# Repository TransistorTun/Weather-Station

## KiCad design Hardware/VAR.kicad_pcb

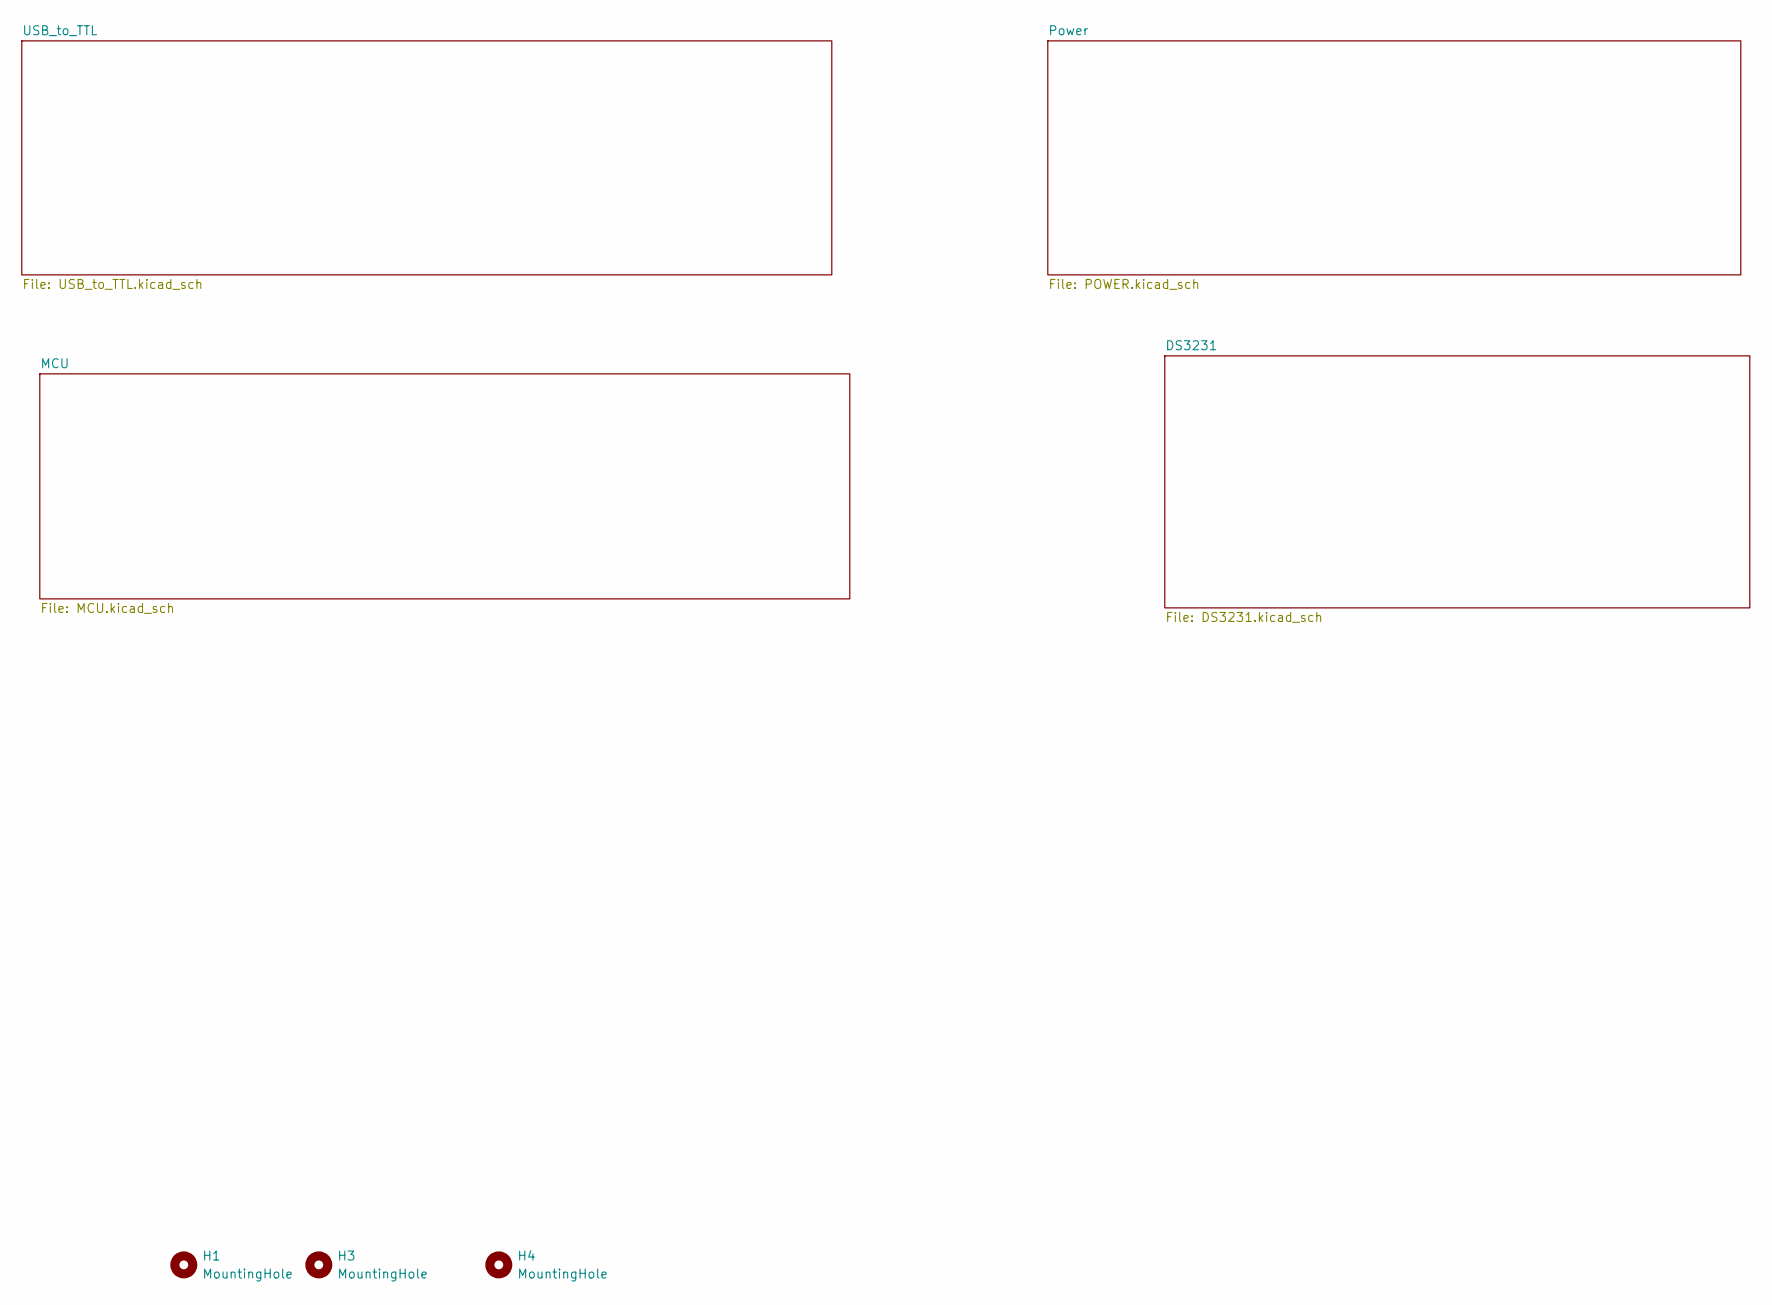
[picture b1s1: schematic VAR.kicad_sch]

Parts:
H1, H3, H4: MountingHole; MountingHole_3.2mm_M3

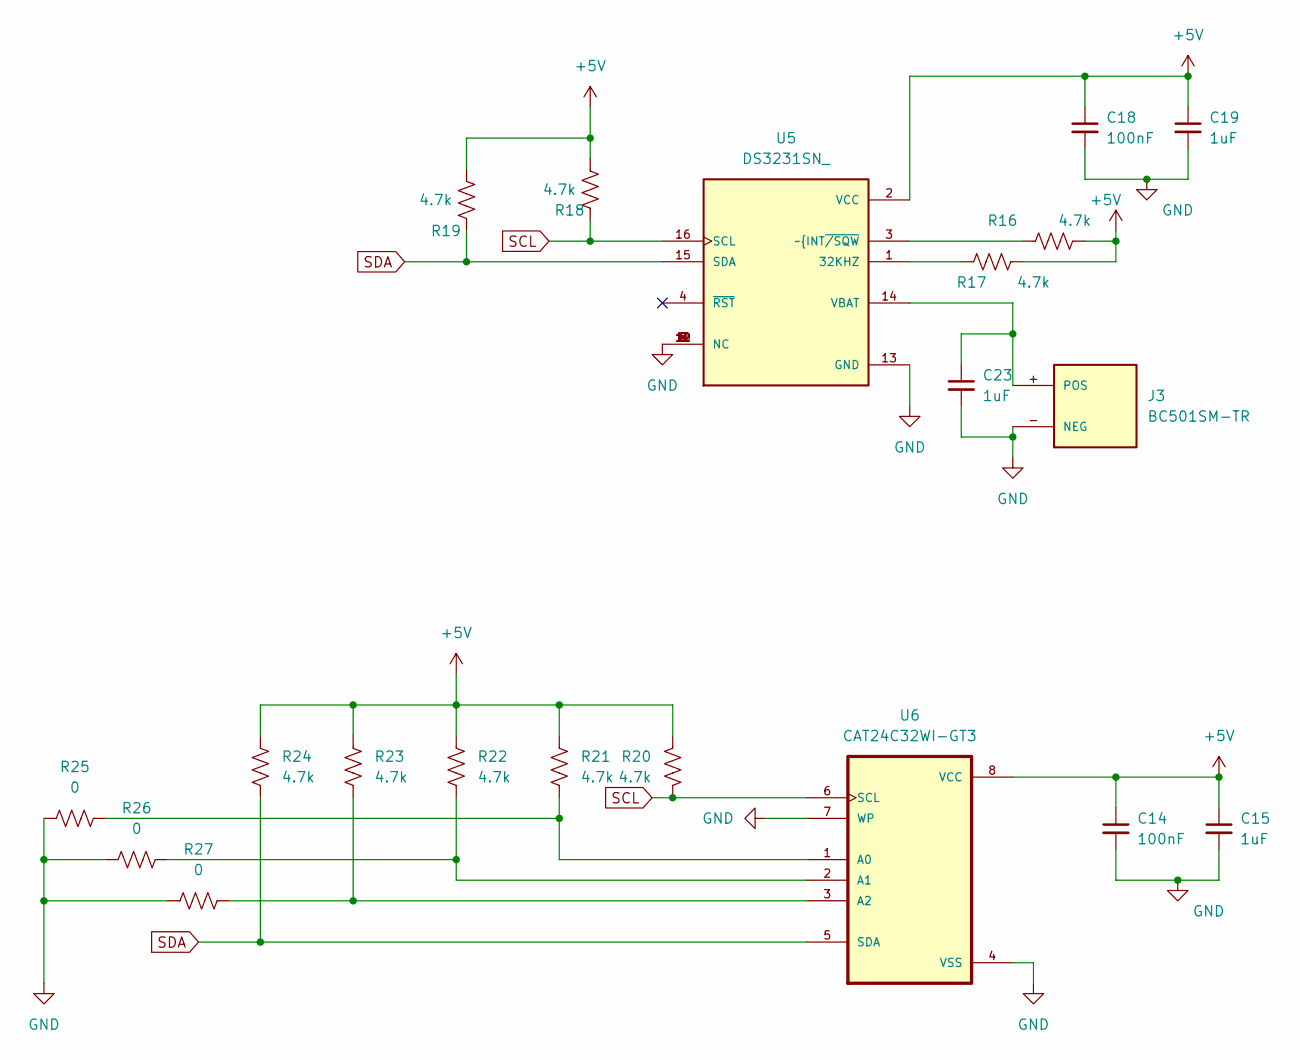
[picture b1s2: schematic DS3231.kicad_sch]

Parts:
C14, C18: 100nF; C_0805_2012Metric_Pad1.18x1.45mm_HandSolder
C15, C19, C23: 1uF; C_0805_2012Metric_Pad1.18x1.45mm_HandSolder
J3: BC501SM-TR; MPD_BC501SM-TR; PARTREV H
R16, R17, R18, R19, R20, R21, R22, R23, R24: 4.7k; R_0805_2012Metric_Pad1.20x1.40mm_HandSolder
R25, R26, R27: 0; R_0805_2012Metric_Pad1.20x1.40mm_HandSolder
U5: DS3231SN_; SOIC127P1032X265-16N; PARTREV 10
U6: CAT24C32WI-GT3; SOIC127P600X175-8N

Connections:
+5V: C14.1, C15.1, C18.1, C19.1, R16.2, R17.2, R18.2, R19.2, R20.1, R21.1, R22.1, R23.1, R24.1, U5.2 (VCC), U6.8 (VCC); also elsewhere on the board
GND: C14.2, C15.2, C18.2, C19.2, C23.2, J3.- (NEG), R25.1, R26.1, R27.1, U5.5 (NC), U5.6 (NC), U5.7 (NC), U5.8 (NC), U5.9 (NC), U5.10 (NC), U5.11 (NC), U5.12 (NC), U5.13 (GND), U6.4 (VSS), U6.7 (WP); also elsewhere on the board
unnamed: C23.1, J3.+ (POS), U5.14 (VBAT)
unnamed: R17.1, U5.1 (32KHZ)
unnamed: R16.1, U5.3 (~INT~{/SQW)
unnamed: R21.2, R25.2, U6.1 (A0)
unnamed: R22.2, R26.2, U6.2 (A1)
unnamed: R23.2, R27.2, U6.3 (A2)
SCL: R18.1, R20.2, U5.16 (SCL), U6.6 (SCL); also elsewhere on the board
SDA: R19.1, R24.2, U5.15 (SDA), U6.5 (SDA); also elsewhere on the board

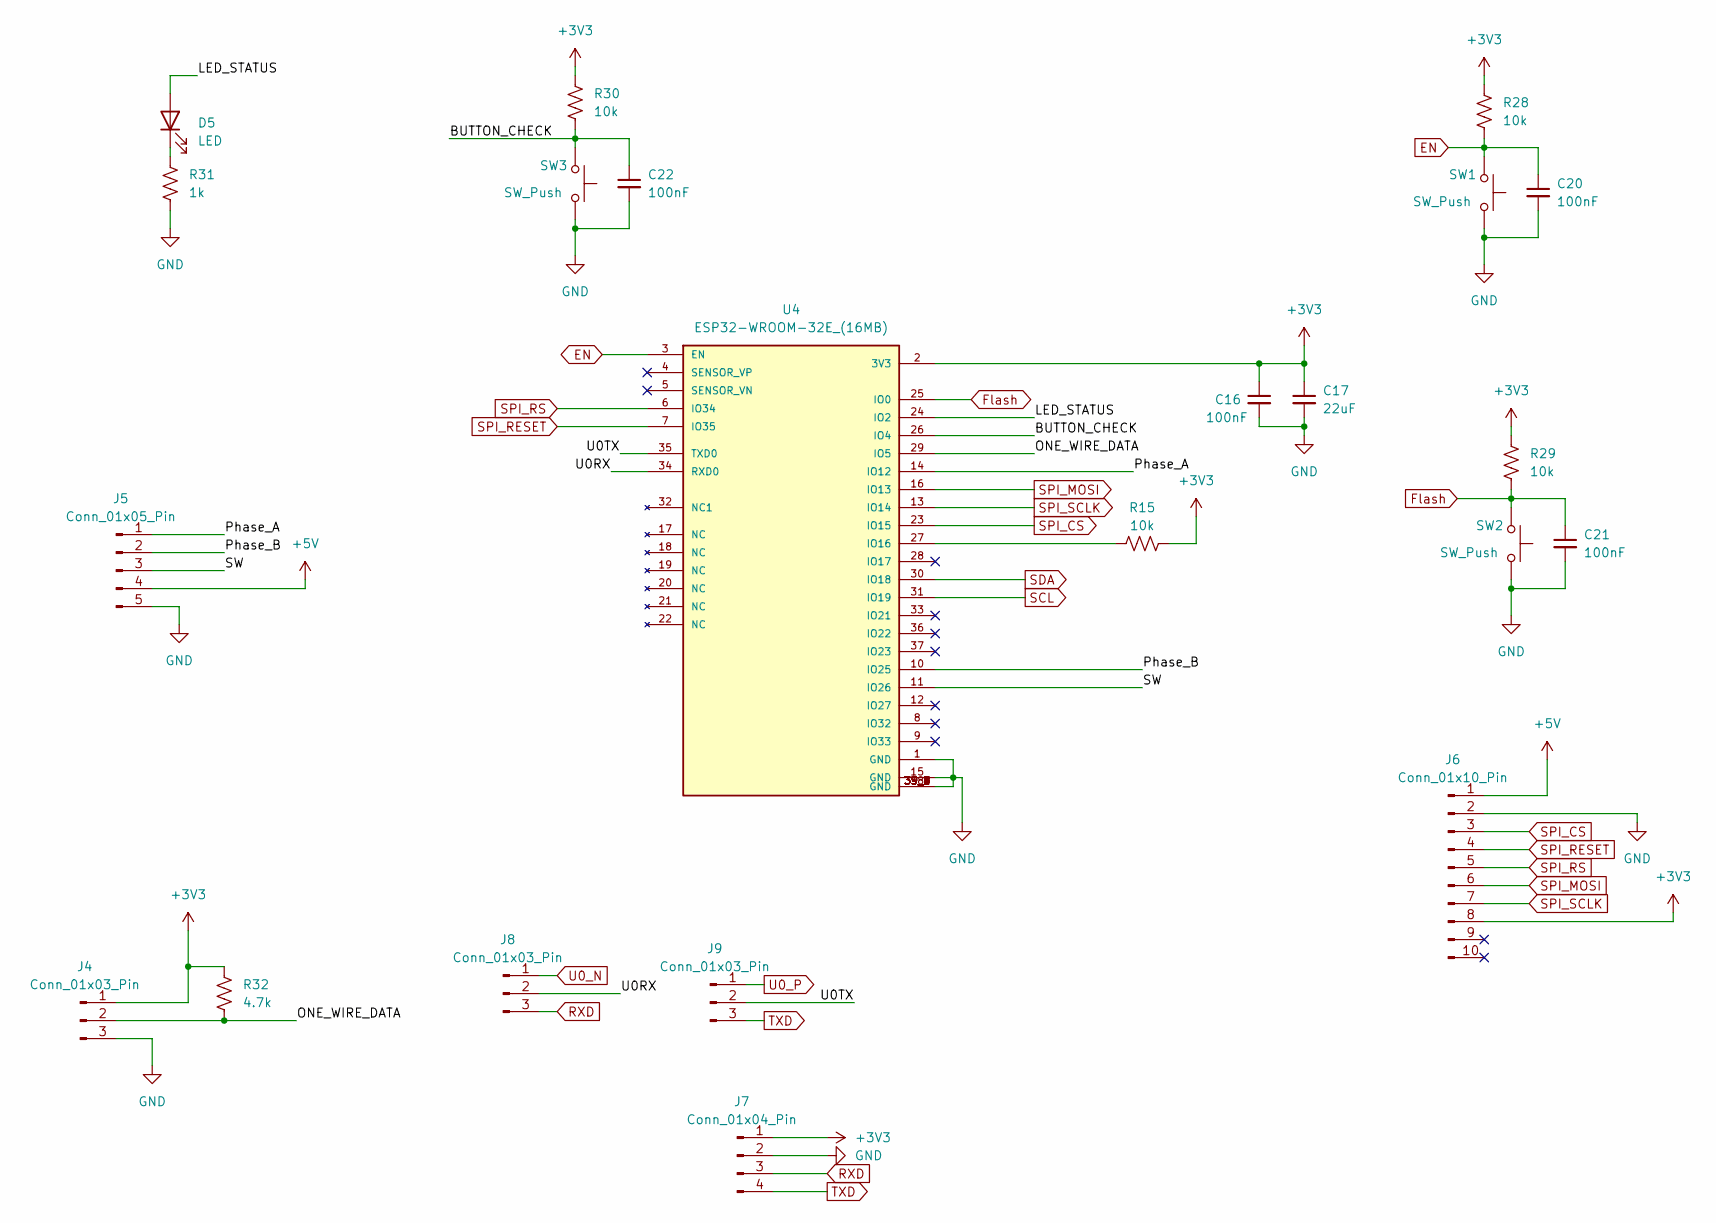
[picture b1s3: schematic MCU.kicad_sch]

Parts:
C16, C20, C21, C22: 100nF; C_0805_2012Metric_Pad1.18x1.45mm_HandSolder
C17: 22uF; C_0805_2012Metric_Pad1.18x1.45mm_HandSolder
D5: LED; LED_0805_2012Metric_Pad1.15x1.40mm_HandSolder
J4, J8, J9: Conn_01x03_Pin; PinHeader_1x03_P2.54mm_Vertical
J5: Conn_01x05_Pin; PinHeader_1x05_P2.54mm_Vertical
J6: Conn_01x10_Pin; PinHeader_1x10_P2.54mm_Vertical
J7: Conn_01x04_Pin; PinHeader_1x04_P2.54mm_Vertical
R15, R28, R29, R30: 10k; R_0805_2012Metric_Pad1.20x1.40mm_HandSolder
R31: 1k; R_0805_2012Metric_Pad1.20x1.40mm_HandSolder
R32: 4.7k; R_0805_2012Metric_Pad1.20x1.40mm_HandSolder
SW1, SW2, SW3: SW_Push; SW_Tactile_SPST_NO_Straight_CK_PTS636Sx25SMTRLFS
U4: ESP32-WROOM-32E_(16MB); XCVR_ESP32-WROOM-32E_(16MB)

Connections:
+3V3: C16.1, C17.1, J4.1, J6.8, J7.1, R15.2, R28.1, R29.1, R30.1, R32.1, U4.2 (3V3); also elsewhere on the board
+5V: J5.4, J6.1; also elsewhere on the board
/MCU/BUTTON_CHECK: C22.1, R30.2, SW3.1, U4.26 (IO4)
/MCU/LED_STATUS: D5.2 (A), U4.24 (IO2)
/MCU/ONE_WIRE_DATA: J4.2, R32.2, U4.29 (IO5)
/MCU/Phase_A: J5.1, U4.14 (IO12)
/MCU/Phase_B: J5.2, U4.10 (IO25)
/MCU/SW: J5.3, U4.11 (IO26)
/MCU/U0RX: J8.2, U4.34 (RXD0)
/MCU/U0TX: J9.2, U4.35 (TXD0)
EN: C20.1, R28.2, SW1.1, U4.3 (EN); also elsewhere on the board
Flash: C21.1, R29.2, SW2.1, U4.25 (IO0); also elsewhere on the board
GND: C16.2, C17.2, C20.2, C21.2, C22.2, J4.3, J5.5, J6.2, J7.2, R31.2, SW1.2, SW2.2, SW3.2, U4.1 (GND), U4.15 (GND), U4.38 (GND), U4.39_1 (GND), U4.39_2 (GND), U4.39_3 (GND), U4.39_4 (GND), U4.39_5 (GND), U4.39_6 (GND), U4.39_7 (GND), U4.39_8 (GND), U4.39_9 (GND), U4.39_10, U4.39_11, U4.39_12, U4.39_13, U4.39_14, U4.39_15, U4.39_16, U4.39_17, U4.39_18, U4.39_19, U4.39_20, U4.39_21; also elsewhere on the board
unnamed: D5.1 (K), R31.1
unnamed: R15.1, U4.27 (IO16)
RXD: J7.3, J8.3
SCL: U4.31 (IO19); also elsewhere on the board
SDA: U4.30 (IO18); also elsewhere on the board
SPI_CS: J6.3, U4.23 (IO15)
SPI_MOSI: J6.6, U4.16 (IO13)
SPI_RESET: J6.4, U4.7 (IO35)
SPI_RS: J6.5, U4.6 (IO34)
SPI_SCLK: J6.7, U4.13 (IO14)
TXD: J7.4, J9.3
U0_N: J8.1; also elsewhere on the board
U0_P: J9.1; also elsewhere on the board

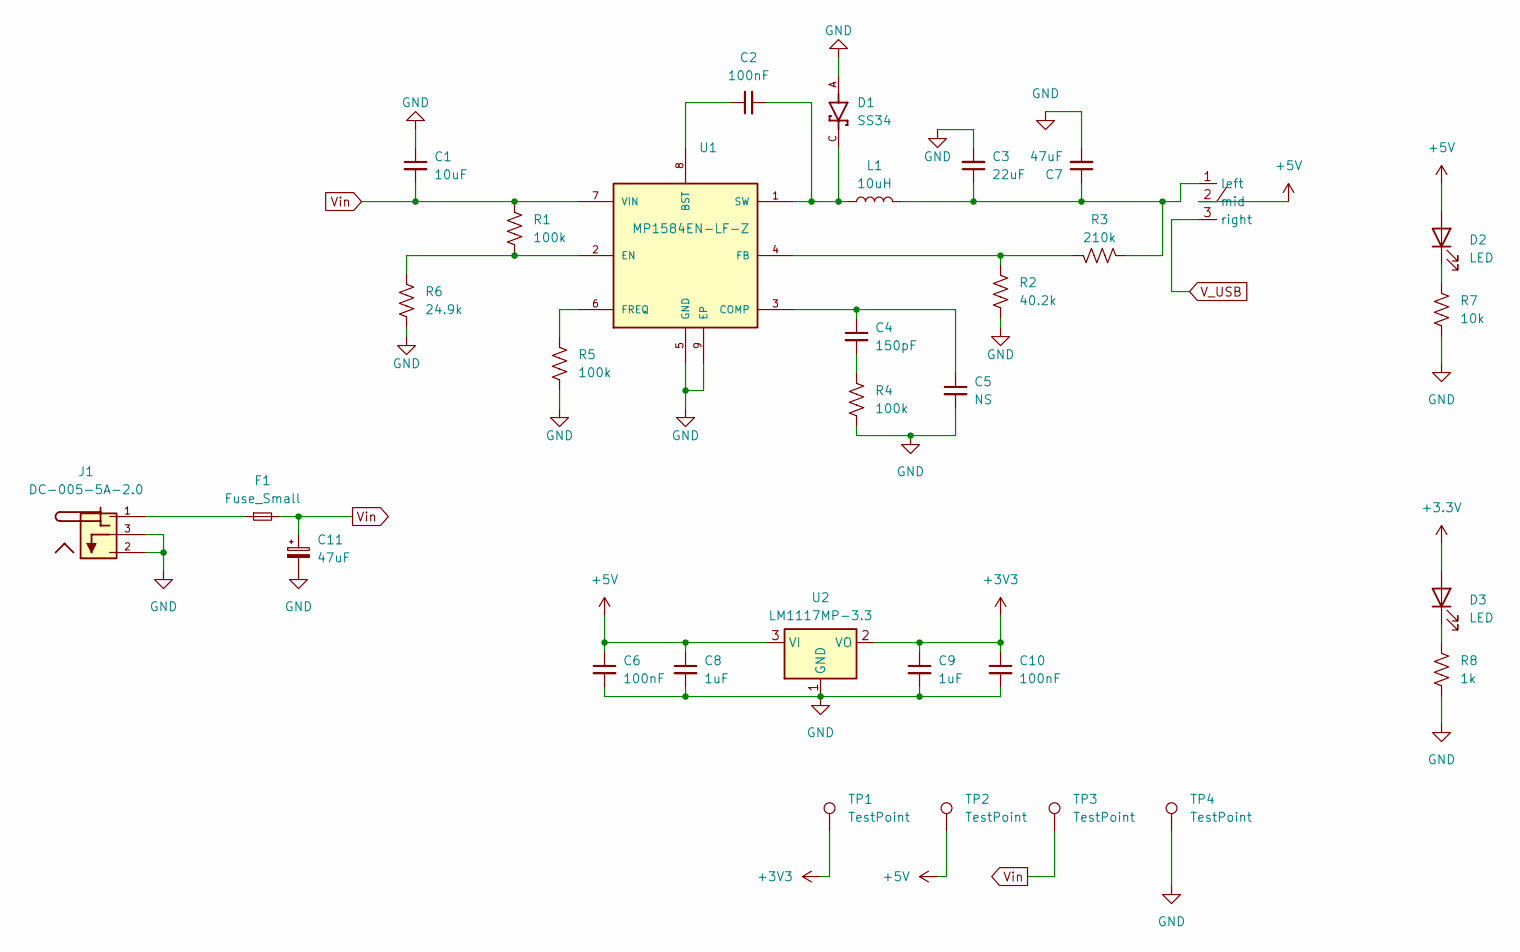
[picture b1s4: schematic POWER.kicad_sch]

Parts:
C1: 10uF; C_0805_2012Metric_Pad1.18x1.45mm_HandSolder
C2, C6, C10: 100nF; C_0805_2012Metric_Pad1.18x1.45mm_HandSolder
C3: 22uF; C_Elec_6.3x5.4
C4: 150pF; C_0805_2012Metric_Pad1.18x1.45mm_HandSolder
C5: NS; C_0805_2012Metric_Pad1.18x1.45mm_HandSolder
C7, C11: 47uF; C_Elec_6.3x5.4
C8, C9: 1uF; C_0805_2012Metric_Pad1.18x1.45mm_HandSolder
D1: SS34; DIOM7959X265N; PARTREV 31 Aug 2016
D2, D3: LED; LED_0805_2012Metric_Pad1.15x1.40mm_HandSolder
F1: Fuse_Small; Fuse_1812_4532Metric_Pad1.30x3.40mm_HandSolder
J1: DC-005-5A-2.0; XKB_DC-005-5A-2.0; PARTREV A0
L1: 10uH; L_Bourns_SRP1038C_10.0x10.0mm
R1, R4, R5: 100k; R_0805_2012Metric_Pad1.20x1.40mm_HandSolder
R2: 40.2k; R_0805_2012Metric_Pad1.20x1.40mm_HandSolder
R3: 210k; R_0805_2012Metric_Pad1.20x1.40mm_HandSolder
R6: 24.9k; R_0805_2012Metric_Pad1.20x1.40mm_HandSolder
R7: 10k; R_0805_2012Metric_Pad1.20x1.40mm_HandSolder
R8: 1k; R_0805_2012Metric_Pad1.20x1.40mm_HandSolder
SW4: SS-12D10
TP1, TP2, TP3, TP4: TestPoint; TestPoint_Loop_D2.54mm_Drill1.5mm_Beaded
U1: MP1584EN-LF-Z; SOIC127P600X170-9N
U2: LM1117MP-3.3; SOT-223-3_TabPin2

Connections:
+3.3V: D3.2 (A)
+3V3: C9.1, C10.1, TP1.1, U2.2 (VO); also elsewhere on the board
+5V: C6.1, C8.1, D2.2 (A), SW4.2 (mid), TP2.1, U2.3 (VI); also elsewhere on the board
GND: C1.1, C3.2, C5.2, C6.2, C7.2, C8.2, C9.2, C10.2, C11.2, D1.A, J1.2, J1.3, R2.2, R4.2, R5.2, R6.2, R7.2, R8.2, TP4.1, U1.5 (GND), U1.9 (EP), U2.1 (GND); also elsewhere on the board
unnamed: C4.2, R4.1
unnamed: D2.1 (K), R7.1
unnamed: D3.1 (K), R8.1
unnamed: F1.1, J1.1
unnamed: C3.1, C7.1, L1.2, R3.1, SW4.1 (left)
unnamed: C2.1, U1.8 (BST)
unnamed: C4.1, C5.1, U1.3 (COMP)
unnamed: R1.2, R6.1, U1.2 (EN)
unnamed: R2.1, R3.2, U1.4 (FB)
unnamed: R5.1, U1.6 (FREQ)
unnamed: C2.2, D1.C, L1.1, U1.1 (SW)
V_USB: SW4.3 (right); also elsewhere on the board
Vin: C1.2, C11.1, F1.2, R1.1, TP3.1, U1.7 (VIN)

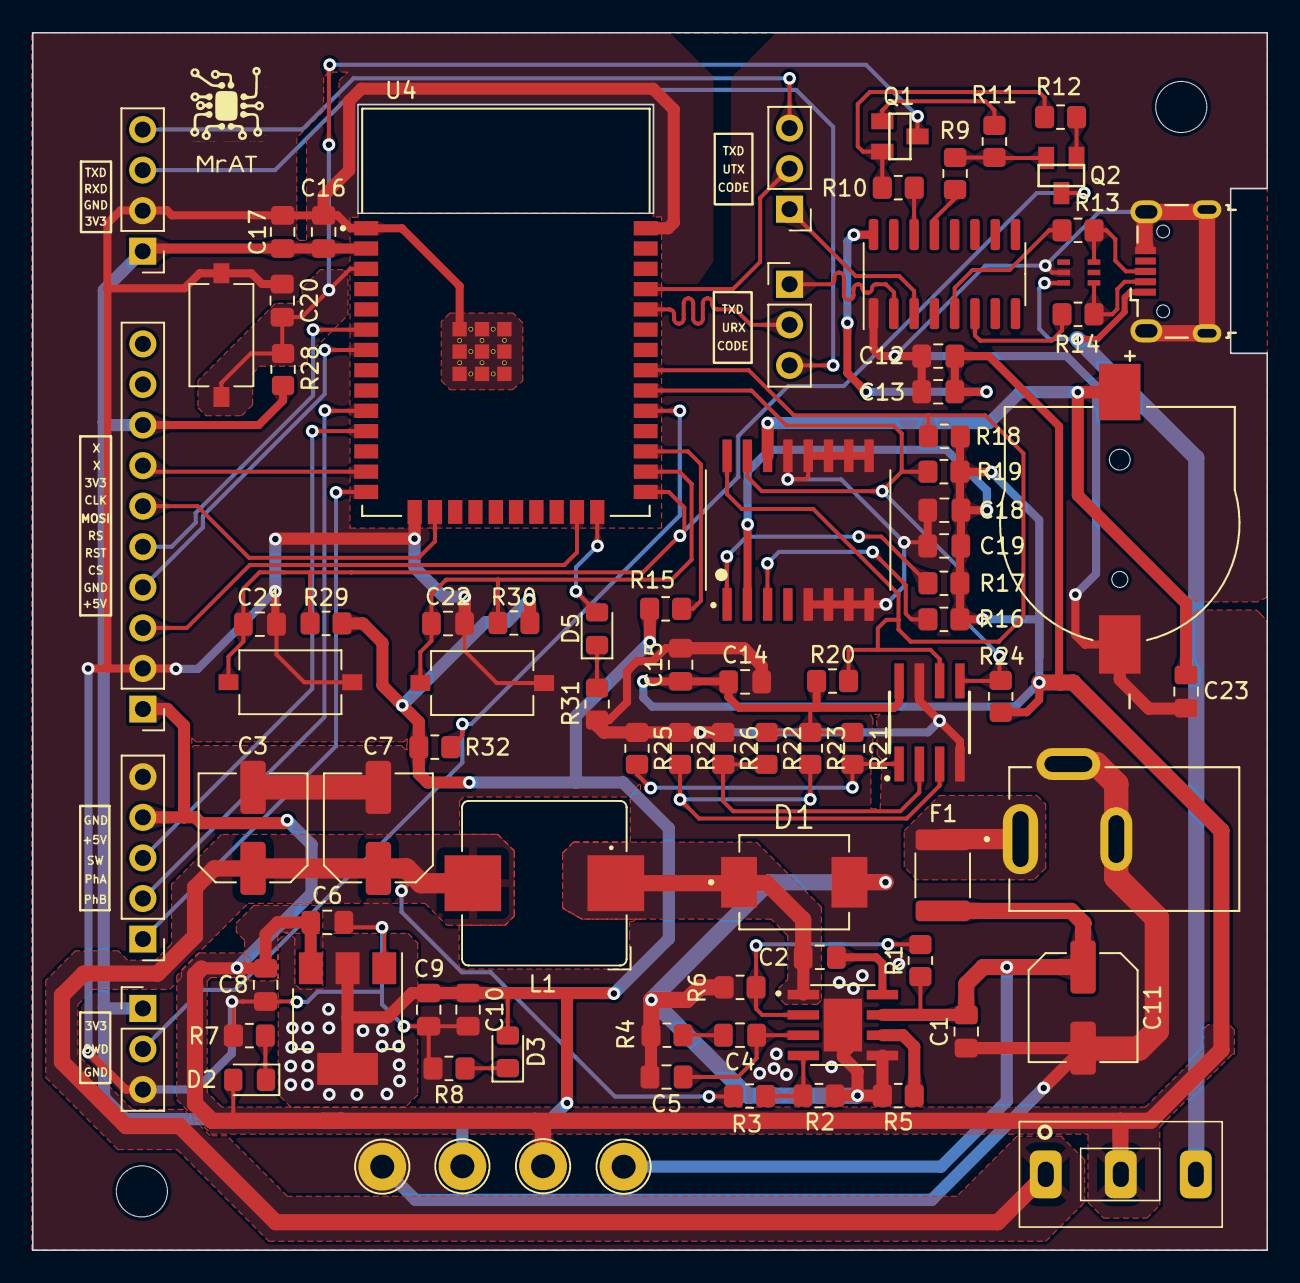
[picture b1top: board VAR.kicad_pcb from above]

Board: 2 copper layers, 77.3 x 76.2 mm, 89 parts (0 on the bottom side), 55 nets.

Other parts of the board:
C12: 22uF; C_0805_2012Metric_Pad1.18x1.45mm_HandSolder
C13: 100nF; C_0805_2012Metric_Pad1.18x1.45mm_HandSolder
D6: SMF05C; SC70-6
J2: USB_B_Micro; USB_Micro-B_Wuerth_629105150521
Q1, Q2: MMBT2222A; SOT23
R9, R10: 22; R_0805_2012Metric_Pad1.20x1.40mm_HandSolder
R11, R12: 10k; R_0805_2012Metric_Pad1.20x1.40mm_HandSolder
R13, R14: 0; R_0805_2012Metric_Pad1.20x1.40mm_HandSolder
U3: CH340C; SOIC-16_3.9x9.9mm_P1.27mm

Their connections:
+5V: C12.1, C13.1, U3.16 (VCC); also elsewhere on the board
/USB_to_TTL/D_N: D6.4, J2.2 (D-), R14.2
/USB_to_TTL/D_P: D6.6, J2.3 (D+), R13.1
DIR: Q2.2, R9.2, R11.2
EN: Q1.3; also elsewhere on the board
Flash: Q2.3; also elsewhere on the board
GND: C12.2, C13.2, D6.2, J2.5 (GND), J2.6 (Shield), U3.1 (GND); also elsewhere on the board
unnamed: Q1.1, R11.1
unnamed: Q2.1, R12.1
unnamed: R13.2, U3.5 (UD+)
unnamed: R14.1, U3.6 (UD-)
unnamed: R9.1, U3.13 (~DTR)
unnamed: R10.1, U3.14 (~RTS)
RTS: Q1.2, R10.2, R12.2
U0_N: U3.2 (TXD); also elsewhere on the board
U0_P: U3.3 (RXD); also elsewhere on the board
V_USB: D6.3, J2.1 (VBUS); also elsewhere on the board
